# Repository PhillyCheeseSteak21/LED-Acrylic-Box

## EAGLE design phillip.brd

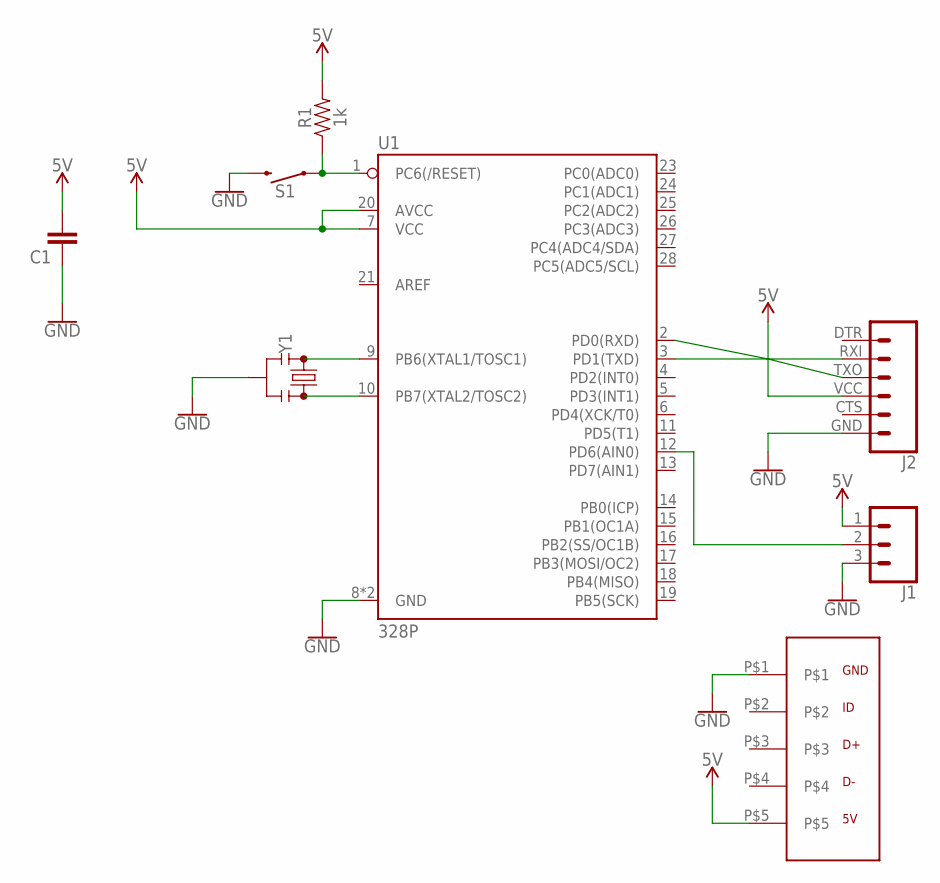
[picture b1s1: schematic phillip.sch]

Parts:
C1: C10/4; C10B4
J1: CONN_03POLAR; MOLEX-1X3
J2: 6_PIN_SERIAL_CABLEPTH; FTDI_BASIC
R1: 1k; AXIAL-0.3
S1: MOMENTARY-SWITCH-SPST-PTH-6.0MM; TACTILE_SWITCH_PTH_6.0MM
U1: 328P; DIP28
U$1: USB_CON1; USB-CON
Y1: RESONATORPTH-7.6X3.8; RESONATOR-PTH-7.6X3.8

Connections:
5V: C1.2, J1.1, J2.VCC (4), R1.P$2 (2), U1.7 (VCC), U1.20 (AVCC), U$1.P$5
GND: C1.1, J1.3, J2.GND (6), S1.3 (2), U1.8 (GND), U1.22 (GND), U$1.P$1, Y1.2
unnamed: R1.P$1 (1), S1.1, U1.1 (PC6(/RESET))
unnamed: U1.10 (PB7(XTAL2/TOSC2)), Y1.3
unnamed: U1.9 (PB6(XTAL1/TOSC1)), Y1.1
unnamed: J1.2, U1.12 (PD6(AIN0))
unnamed: J2.TXO (3), U1.2 (PD0(RXD))
unnamed: J2.RXI (2), U1.3 (PD1(TXD))

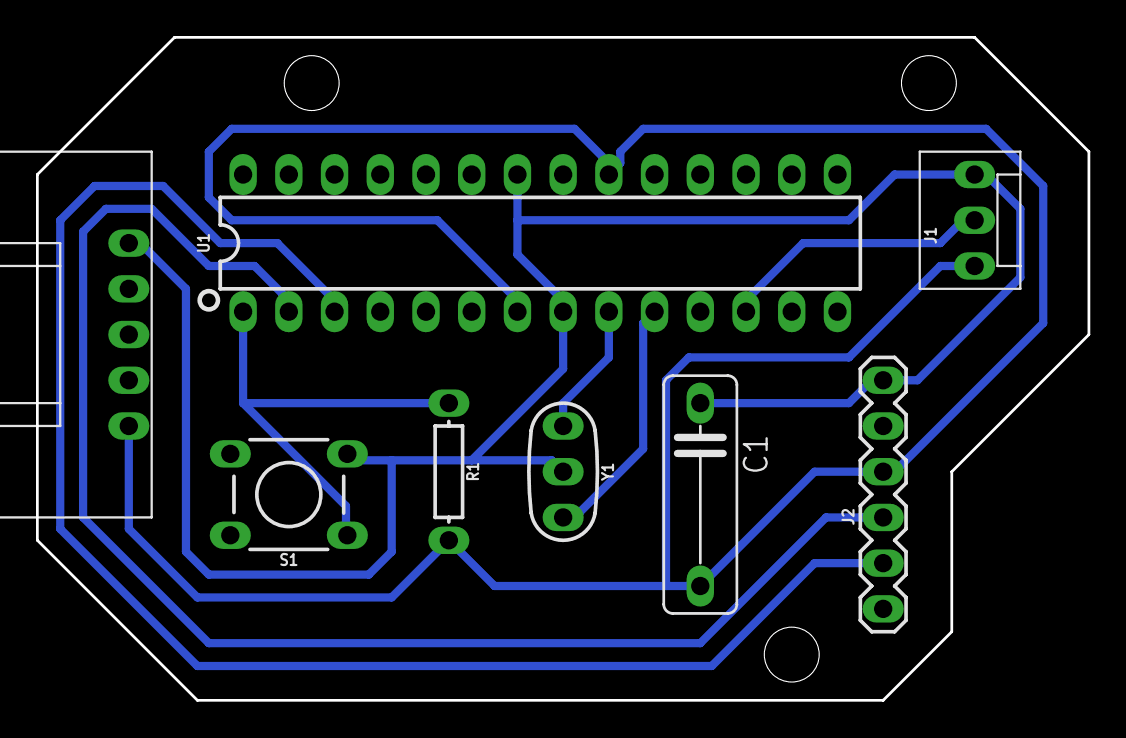
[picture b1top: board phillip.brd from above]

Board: 2 copper layers, 58.4 x 36.8 mm, 8 parts (0 on the bottom side), 8 nets.

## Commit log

2019-01-22 I put all of my files intothe repository for the LED Acrylic project
2019-02-15 Create Cost Sheet

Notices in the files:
parts and their libraries:
SparkFun-PowerSymbols: Licensing: Creative Commons ShareAlike 4.0 International - https://creativecommons.org/licenses/by-sa/4.0
